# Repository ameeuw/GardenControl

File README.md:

# GardenControl

This project combines three mechanical relay switches with modular sensor ports in a case to allow for automated watering, lighting and nutritioning of plants.

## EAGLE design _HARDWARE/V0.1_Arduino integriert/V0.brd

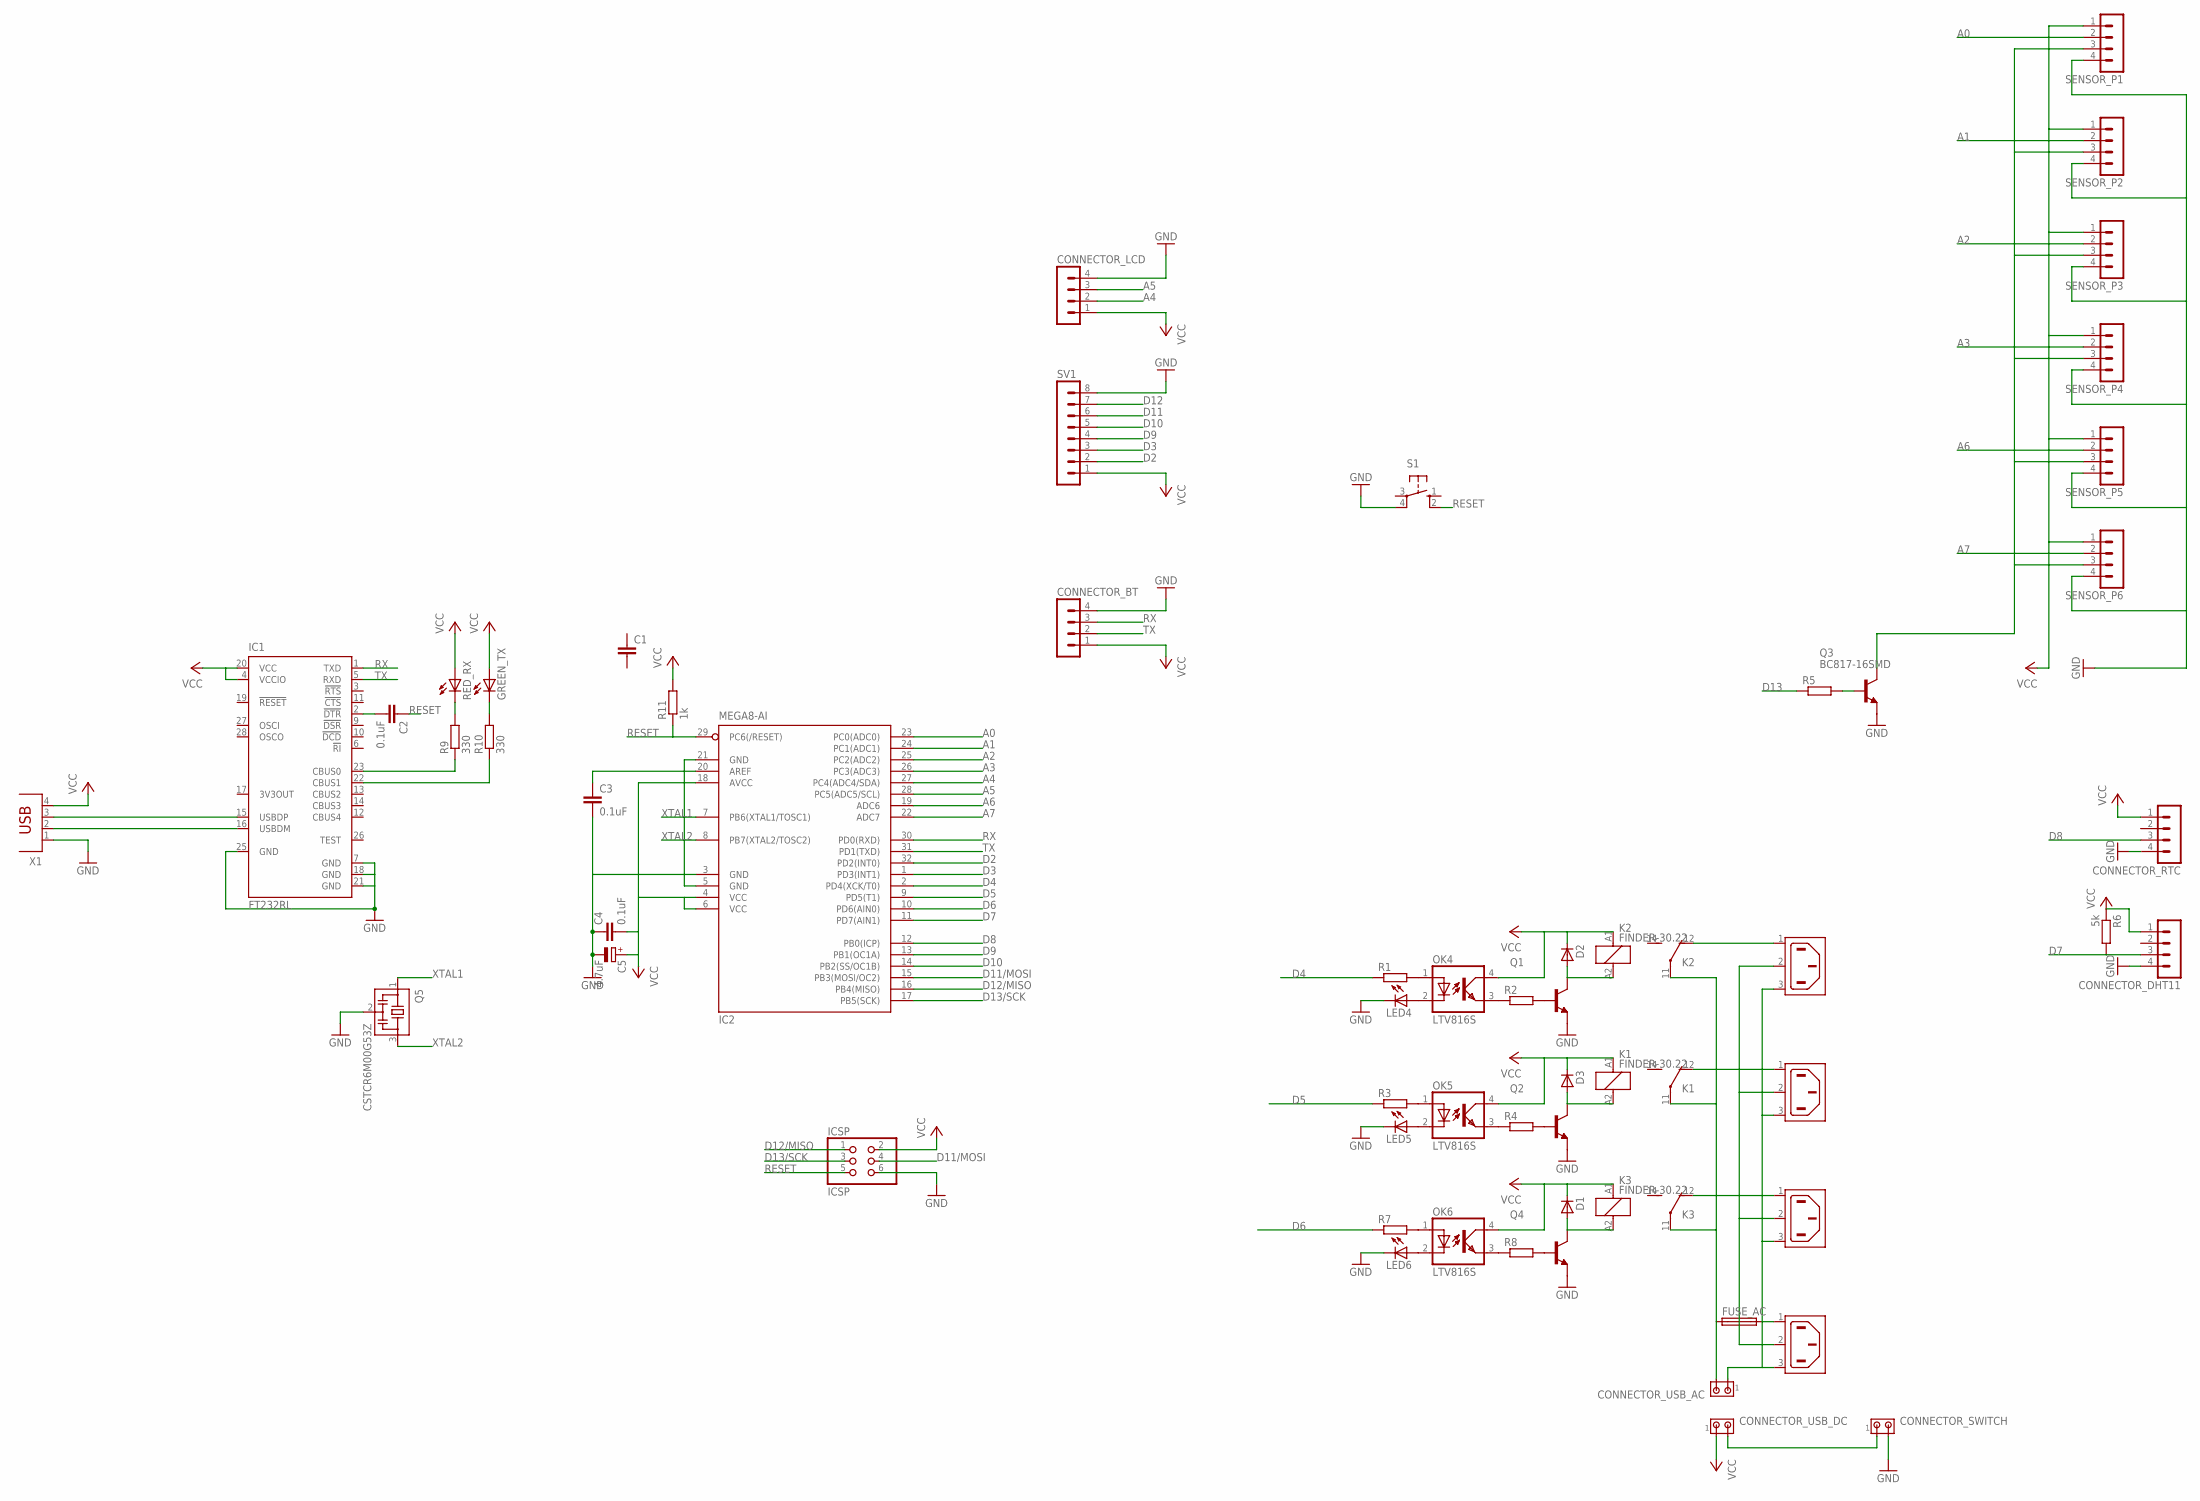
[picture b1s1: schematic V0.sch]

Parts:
C1: C; C0805
C2, C3, C4: 0.1uF; C0805
C5: 4.7uF; 085CS_1AW
CONNECTOR_BT: MA04-1
CONNECTOR_DHT11: MA04-1
CONNECTOR_LCD: MA04-1
CONNECTOR_RTC: MA04-1
CONNECTOR_SWITCH: MTA02-100; 10X02MTA
CONNECTOR_USB_AC: MTA02-100; 10X02MTA
CONNECTOR_USB_DC: MTA02-100; 10X02MTA
D1, D2, D3: DIODE_E-; DIODE_SMB
FUSE_AC: SH22,5
GREEN_TX: LEDCHIPLED_0805; CHIPLED_0805
IC1: FT232RL; SSOP28
IC2: MEGA8-AI; TQFP32-08
ICSP: ICSP; 2X03SMD
IN_AC: 6ESRM-P
K1, K2, K3: FINDER-30.22
LED4, LED5, LED6: LEDCHIPLED_0805; CHIPLED_0805
OK4, OK5, OK6: LTV816S; SMD4
OUT_LIGHT: 6ESRM-P
OUT_PUMP, OUT_PUMP1: 6ESRM-P
Q1, Q2, Q4: BC847ASMD; SOT23
Q3: BC817-16SMD; SOT23-BEC
Q5: CSTCR6M00G53Z; CSTCR6M
R1, R2, R3, R4, R5, R7, R8: R; R0805
R6: 5k; R0805
R9, R10: 330; R0805
R11: 1k; R0805
RED_RX: LEDCHIPLED_0805; CHIPLED_0805
S1: 10-XX; B3F-10XX
SENSOR_P1, SENSOR_P2, SENSOR_P3, SENSOR_P4, SENSOR_P5, SENSOR_P6: MA04-1
SV1: MA08-1
X1: PN61729

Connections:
A0: IC2.23 (PC0(ADC0)), SENSOR_P1.2
A1: IC2.24 (PC1(ADC1)), SENSOR_P2.2
A2: IC2.25 (PC2(ADC2)), SENSOR_P3.2
A3: IC2.26 (PC3(ADC3)), SENSOR_P4.2
A4: CONNECTOR_LCD.2, IC2.27 (PC4(ADC4/SDA))
A5: CONNECTOR_LCD.3, IC2.28 (PC5(ADC5/SCL))
A6: IC2.19 (ADC6), SENSOR_P5.2
A7: IC2.22 (ADC7), SENSOR_P6.2
AVCC: IC2.18 (AVCC)
D2: IC2.32 (PD2(INT0)), SV1.2
D3: IC2.1 (PD3(INT1)), SV1.3
D4: IC2.2 (PD4(XCK/T0)), R1.1
D5: IC2.9 (PD5(T1)), R3.1
D6: IC2.10 (PD6(AIN0)), R7.1
D7: CONNECTOR_DHT11.3, IC2.11 (PD7(AIN1)), R6.2
D8: CONNECTOR_RTC.3, IC2.12 (PB0(ICP))
D9: IC2.13 (PB1(OC1A)), SV1.4
D10: IC2.14 (PB2(SS/OC1B)), SV1.5
D11: SV1.6
D11/MOSI: IC2.15 (PB3(MOSI/OC2)), ICSP.4
D12: SV1.7
D12/MISO: IC2.16 (PB4(MISO)), ICSP.1
D13: R5.1
D13/SCK: IC2.17 (PB5(SCK)), ICSP.3
GND: C3.2, C4.1, C5.-, CONNECTOR_BT.4, CONNECTOR_DHT11.4, CONNECTOR_LCD.4, CONNECTOR_RTC.4, CONNECTOR_SWITCH.2, IC1.7 (GND), IC1.18 (GND), IC1.21 (GND), IC1.25 (GND), IC2.3 (GND), IC2.5 (GND), IC2.21 (GND), ICSP.6, LED4.C, LED5.C, LED6.C, Q1.2 (E), Q2.2 (E), Q3.E, Q4.2 (E), Q5.2, S1.4 (P1), SENSOR_P1.4, SENSOR_P2.4, SENSOR_P3.4, SENSOR_P4.4, SENSOR_P5.4, SENSOR_P6.4, SV1.8, X1.1
unnamed: OK4.1 (A), R1.2
unnamed: OK5.1 (A), R3.2
unnamed: OK6.1 (A), R7.2
unnamed: D2.A (C), K2.A2 (2), Q1.3 (C)
unnamed: R9.2, RED_RX.C
unnamed: Q1.1 (B), R2.2
unnamed: CONNECTOR_USB_AC.2, FUSE_AC.1, K1.11, K2.11, K3.11
unnamed: IN_AC.2 (SH), OUT_LIGHT.2 (SH), OUT_PUMP.2 (SH), OUT_PUMP1.2 (SH)
unnamed: LED4.A, OK4.2 (C)
unnamed: FUSE_AC.2, IN_AC.1 (AC1)
unnamed: LED5.A, OK5.2 (C)
unnamed: LED6.A, OK6.2 (C)
unnamed: D3.A (C), K1.A2 (2), Q2.3 (C)
unnamed: GREEN_TX.C, R10.2
unnamed: Q2.1 (B), R4.2
unnamed: K1.12 (O), OUT_PUMP.1 (AC1)
unnamed: K2.12 (O), OUT_LIGHT.1 (AC1)
unnamed: CONNECTOR_USB_AC.1, IN_AC.3 (AC2), OUT_LIGHT.3 (AC2), OUT_PUMP.3 (AC2), OUT_PUMP1.3 (AC2)
unnamed: Q3.C, SENSOR_P1.3, SENSOR_P2.3, SENSOR_P3.3, SENSOR_P4.3, SENSOR_P5.3, SENSOR_P6.3
unnamed: Q3.B, R5.2
unnamed: OK4.3 (EMIT), R2.1
unnamed: OK5.3 (EMIT), R4.1
unnamed: C2.2, IC1.2 (!DTR)
unnamed: IC1.23 (CBUS0), R9.1
unnamed: OK6.3 (EMIT), R8.1
unnamed: D1.A (C), K3.A2 (2), Q4.3 (C)
unnamed: IC1.22 (CBUS1), R10.1
unnamed: Q4.1 (B), R8.2
unnamed: K3.12 (O), OUT_PUMP1.1 (AC1)
unnamed: CONNECTOR_SWITCH.1, CONNECTOR_USB_DC.2
unnamed: IC1.15 (USBDP), X1.3
unnamed: IC1.16 (USBDM), X1.2
RESET: C2.1, IC2.29 (PC6(/RESET)), ICSP.5, R11.1, S1.2 (S1)
RX: CONNECTOR_BT.3, IC1.1 (TXD), IC2.30 (PD0(RXD))
TX: CONNECTOR_BT.2, IC1.5 (RXD), IC2.31 (PD1(TXD))
VCC: C4.2, C5.+, CONNECTOR_BT.1, CONNECTOR_DHT11.1, CONNECTOR_LCD.1, CONNECTOR_RTC.1, CONNECTOR_USB_DC.1, D1.C (A), D2.C (A), D3.C (A), GREEN_TX.A, IC1.4 (VCCIO), IC1.20 (VCC), IC2.4 (VCC), IC2.6 (VCC), ICSP.2, K1.A1 (1), K2.A1 (1), K3.A1 (1), OK4.4 (COL), OK5.4 (COL), OK6.4 (COL), R6.1, R11.2, RED_RX.A, SENSOR_P1.1, SENSOR_P2.1, SENSOR_P3.1, SENSOR_P4.1, SENSOR_P5.1, SENSOR_P6.1, SV1.1, X1.4
XTAL1: IC2.7 (PB6(XTAL1/TOSC1)), Q5.1
XTAL2: IC2.8 (PB7(XTAL2/TOSC2)), Q5.3

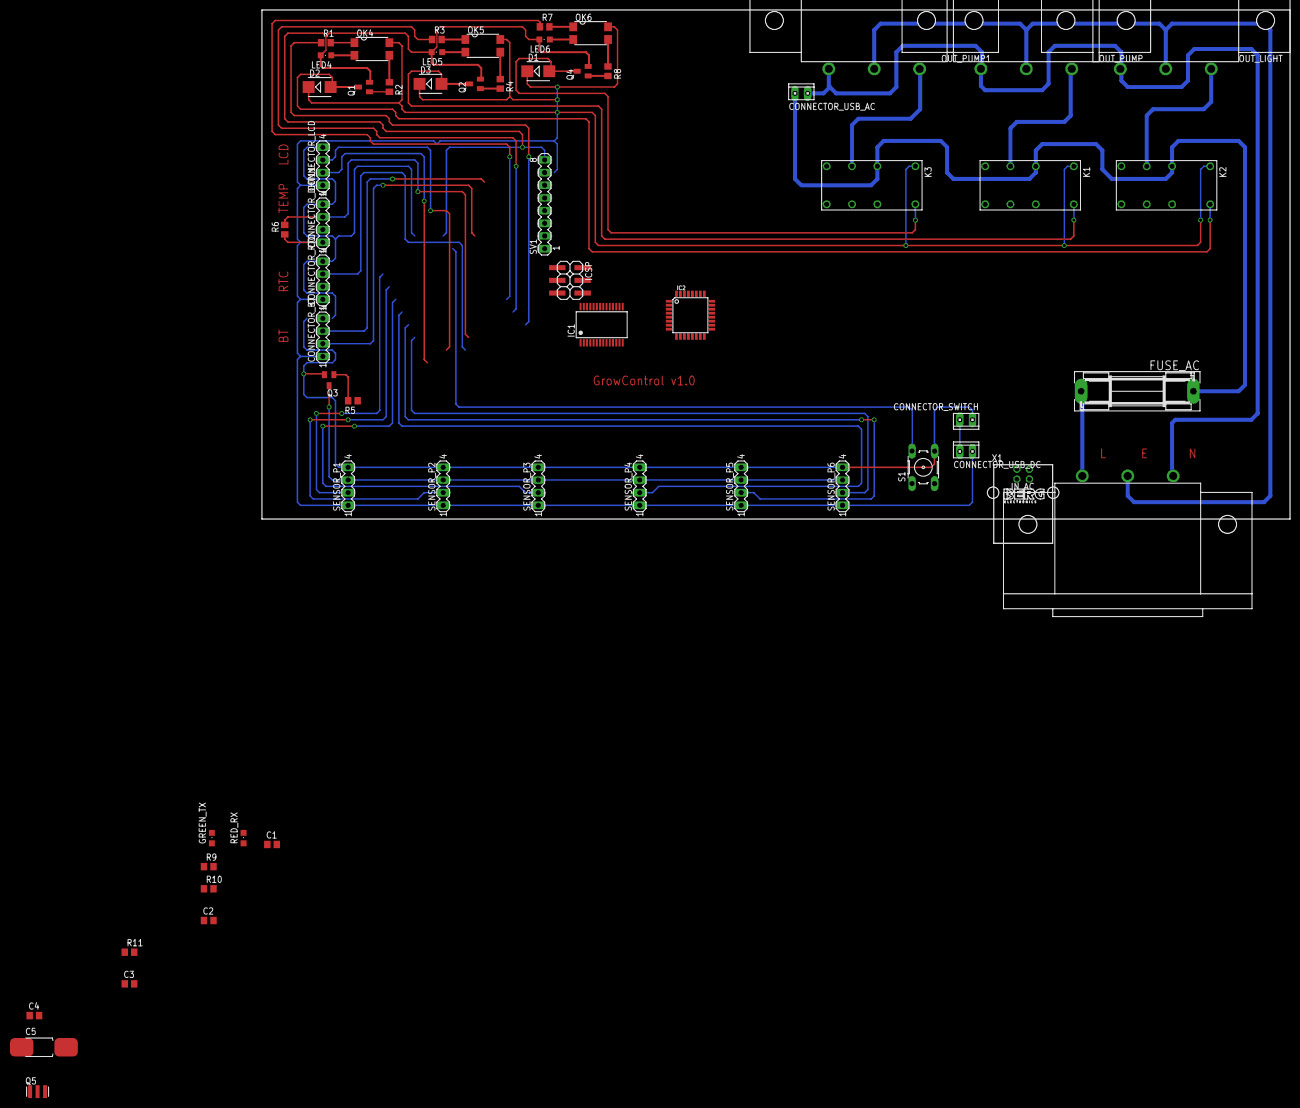
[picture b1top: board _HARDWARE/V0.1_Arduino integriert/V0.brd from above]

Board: 2 copper layers, 206.0 x 102.0 mm, 59 parts (0 on the bottom side), 59 nets.

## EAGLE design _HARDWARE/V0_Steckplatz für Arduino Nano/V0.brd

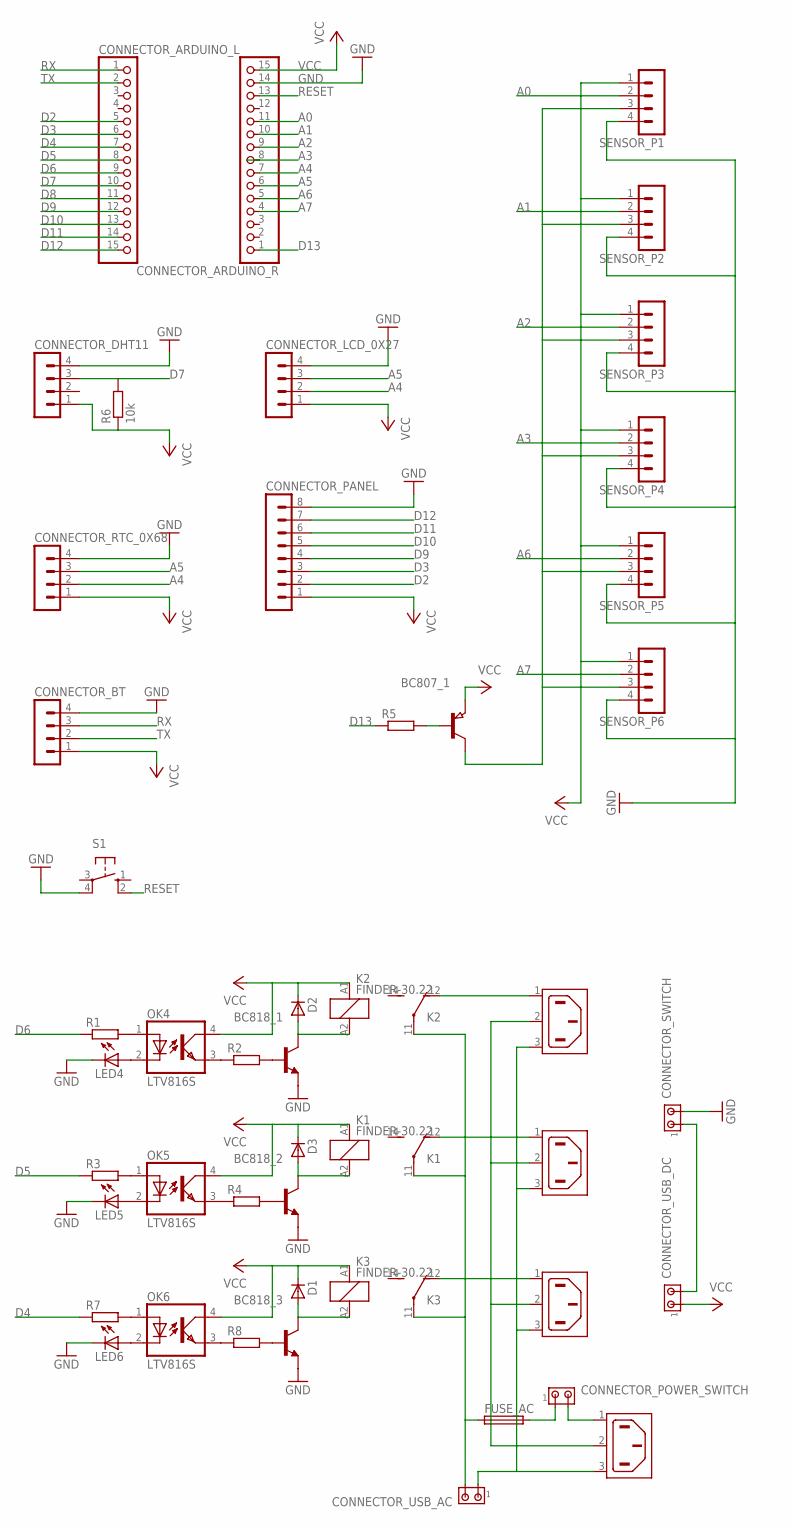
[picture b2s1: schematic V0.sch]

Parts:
BC807_1: PNP-TRANSISTOR_SOT23; SOT23
BC818_1, BC818_2, BC818_3: BC847ASMD; SOT23
CONNECTOR_ARDUINO_L: PINHD-1X15; 1X15
CONNECTOR_ARDUINO_R: PINHD-1X15; 1X15
CONNECTOR_BT: MA04-1
CONNECTOR_DHT11: MA04-1
CONNECTOR_LCD_0X27: MA04-1
CONNECTOR_PANEL: MA08-1
CONNECTOR_POWER_SWITCH: MTA02-100; 10X02MTA
CONNECTOR_RTC_0X68: MA04-1
CONNECTOR_SWITCH: MTA02-100; 10X02MTA
CONNECTOR_USB_AC: MTA02-100; 10X02MTA
CONNECTOR_USB_DC: MTA02-100; 10X02MTA
D1, D2, D3: DIODE_E-; DIODE_SMB
FUSE_AC: SH22,5
IN_AC: 6ESRM-P
K1, K2, K3: FINDER-30.22
LED4, LED5, LED6: LEDCHIPLED_0805; CHIPLED_0805
OK4, OK5, OK6: LTV816S; SMD4
OUT_LIGHT: 6ESRM-P
OUT_PUMP, OUT_PUMP1: 6ESRM-P
R1, R2, R3, R4, R5, R7, R8: R; R0805
R6: 10k; R0805
S1: 10-XX; B3F-10XX
SENSOR_P1, SENSOR_P2, SENSOR_P3, SENSOR_P4, SENSOR_P5, SENSOR_P6: MA04-1

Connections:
A0: CONNECTOR_ARDUINO_R.11, SENSOR_P1.2
A1: CONNECTOR_ARDUINO_R.10, SENSOR_P2.2
A2: CONNECTOR_ARDUINO_R.9, SENSOR_P3.2
A3: CONNECTOR_ARDUINO_R.8, SENSOR_P4.2
A4: CONNECTOR_ARDUINO_R.7, CONNECTOR_LCD_0X27.2, CONNECTOR_RTC_0X68.2
A5: CONNECTOR_ARDUINO_R.6, CONNECTOR_LCD_0X27.3, CONNECTOR_RTC_0X68.3
A6: CONNECTOR_ARDUINO_R.5, SENSOR_P5.2
A7: CONNECTOR_ARDUINO_R.4, SENSOR_P6.2
D2: CONNECTOR_ARDUINO_L.5, CONNECTOR_PANEL.2
D3: CONNECTOR_ARDUINO_L.6, CONNECTOR_PANEL.3
D4: CONNECTOR_ARDUINO_L.7, R7.1
D5: CONNECTOR_ARDUINO_L.8, R3.1
D6: CONNECTOR_ARDUINO_L.9, R1.1
D7: CONNECTOR_ARDUINO_L.10, CONNECTOR_DHT11.3, R6.2
D8: CONNECTOR_ARDUINO_L.11
D9: CONNECTOR_ARDUINO_L.12, CONNECTOR_PANEL.4
D10: CONNECTOR_ARDUINO_L.13, CONNECTOR_PANEL.5
D11: CONNECTOR_ARDUINO_L.14, CONNECTOR_PANEL.6
D12: CONNECTOR_ARDUINO_L.15, CONNECTOR_PANEL.7
D13: CONNECTOR_ARDUINO_R.1, R5.1
GND: BC818_1.2 (E), BC818_2.2 (E), BC818_3.2 (E), CONNECTOR_ARDUINO_R.14, CONNECTOR_BT.4, CONNECTOR_DHT11.4, CONNECTOR_LCD_0X27.4, CONNECTOR_PANEL.8, CONNECTOR_RTC_0X68.4, CONNECTOR_SWITCH.2, LED4.C, LED5.C, LED6.C, S1.4 (P1), SENSOR_P1.4, SENSOR_P2.4, SENSOR_P3.4, SENSOR_P4.4, SENSOR_P5.4, SENSOR_P6.4
unnamed: OK4.1 (A), R1.2
unnamed: OK5.1 (A), R3.2
unnamed: OK6.1 (A), R7.2
unnamed: BC818_1.3 (C), D2.A (C), K2.A2 (2)
unnamed: BC818_1.1 (B), R2.2
unnamed: CONNECTOR_USB_AC.2, FUSE_AC.1, K1.11, K2.11, K3.11
unnamed: IN_AC.2 (SH), OUT_LIGHT.2 (SH), OUT_PUMP.2 (SH), OUT_PUMP1.2 (SH)
unnamed: LED4.A, OK4.2 (C)
unnamed: CONNECTOR_POWER_SWITCH.2, IN_AC.1 (AC1)
unnamed: LED5.A, OK5.2 (C)
unnamed: LED6.A, OK6.2 (C)
unnamed: BC818_2.3 (C), D3.A (C), K1.A2 (2)
unnamed: CONNECTOR_POWER_SWITCH.1, FUSE_AC.2
unnamed: BC818_2.1 (B), R4.2
unnamed: K1.12 (O), OUT_PUMP.1 (AC1)
unnamed: K2.12 (O), OUT_LIGHT.1 (AC1)
unnamed: CONNECTOR_USB_AC.1, IN_AC.3 (AC2), OUT_LIGHT.3 (AC2), OUT_PUMP.3 (AC2), OUT_PUMP1.3 (AC2)
unnamed: BC807_1.3 (C), SENSOR_P1.3, SENSOR_P2.3, SENSOR_P3.3, SENSOR_P4.3, SENSOR_P5.3, SENSOR_P6.3
unnamed: BC807_1.1 (B), R5.2
unnamed: OK4.3 (EMIT), R2.1
unnamed: OK5.3 (EMIT), R4.1
unnamed: OK6.3 (EMIT), R8.1
unnamed: BC818_3.3 (C), D1.A (C), K3.A2 (2)
unnamed: BC818_3.1 (B), R8.2
unnamed: K3.12 (O), OUT_PUMP1.1 (AC1)
unnamed: CONNECTOR_SWITCH.1, CONNECTOR_USB_DC.2
RESET: CONNECTOR_ARDUINO_R.13, S1.2 (S1)
RX: CONNECTOR_ARDUINO_L.1, CONNECTOR_BT.3
TX: CONNECTOR_ARDUINO_L.2, CONNECTOR_BT.2
VCC: BC807_1.2 (E), CONNECTOR_ARDUINO_R.15, CONNECTOR_BT.1, CONNECTOR_DHT11.1, CONNECTOR_LCD_0X27.1, CONNECTOR_PANEL.1, CONNECTOR_RTC_0X68.1, CONNECTOR_USB_DC.1, D1.C (A), D2.C (A), D3.C (A), K1.A1 (1), K2.A1 (1), K3.A1 (1), OK4.4 (COL), OK5.4 (COL), OK6.4 (COL), R6.1, SENSOR_P1.1, SENSOR_P2.1, SENSOR_P3.1, SENSOR_P4.1, SENSOR_P5.1, SENSOR_P6.1

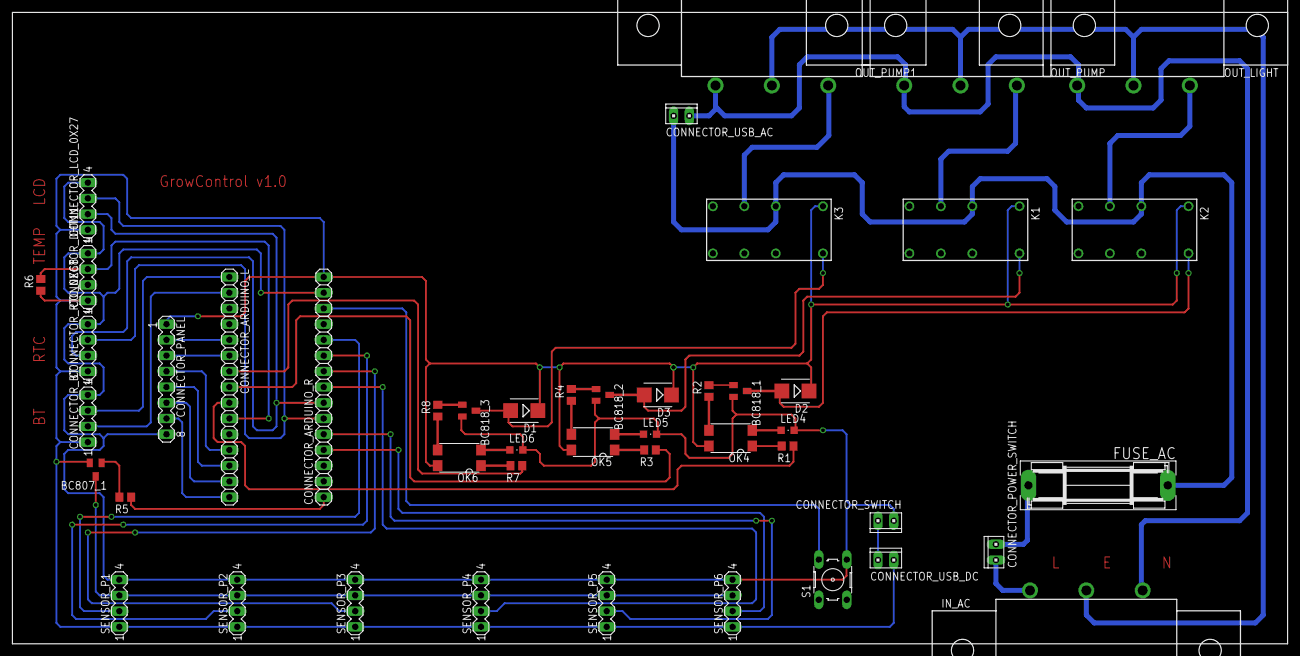
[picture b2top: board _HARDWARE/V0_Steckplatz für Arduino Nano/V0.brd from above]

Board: 2 copper layers, 206.0 x 102.0 mm, 47 parts (0 on the bottom side), 50 nets.

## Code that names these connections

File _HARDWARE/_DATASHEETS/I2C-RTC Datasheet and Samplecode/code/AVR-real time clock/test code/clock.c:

//Function: Display: seconds, minutes, weeks, days, date, month, year. Can show :2000-2099.
//Note: DS1307 to read and write are the BCD code, the use of a swap between the decimal and BCD code.
//Platform£ºatmega64
//fuse bytes£º
//		  low byte£º0xc1
//		  high byte£º0xd9
//		  extend£º0xFF
//		  Lock byte£º0xff
//Crystal Oscillator: Internal RC oscillator 1MHz
//Time: July 27, 2012
#include<avr/io.h>
#include <macros.h>
#include <avr/wdt.h>
#define uint unsigned int 
#define uchar unsigned char
//sda=PD1;//;TWI Data transmission bit
//scl=PD0;//;TWI Clock control state flag
//RS=PC0;//define the I / O hardware interface of LCD1602
//RW=PC1;//define the I / O hardware interface 0f LCD1602 
//E=PC2; //define the I / O hardware interface 0f LCD1602 
uchar count;
uchar string3[]="Time:  :  :     ";
uchar string4[]="20  .  .  week: ";
uchar Hours=16;//Definition of hours
uchar Minutes=21;//Definition of minutes
uchar Seconds=0;//Definition of seconds

uint  Year=12;//Definition of year
uchar Month=7;//Definition of month
uchar Date=27;//Definition of date
uchar Weeks=5;//Definition of weeks 

uchar DispBuf[16]; //16 bytes of display buffer
uchar disp_tab[]={'0','1','2','3','4','5','6','7','8','9'};

#define START 		0X08   //start() has been successfully sent
#define RESTART 	0X10 //The restart() has been successfully sent
#define MT_SLA_ACK 	0X18 //Load data has been sent ack()
#define MT_SLA_NACK 0X20 //Load data has been sent nack()
#define MT_DAT_ACK 	0X28  //Data has been sent ack()
#define MT_DAT_NACK 0X30 //Data has been sent nack()
#define SL_SLA_ACK 	0X40 //Data has been loaded from the machine to send ack()
#define SL_SLA_NACK 0X48 //Data has been loaded from the machine to send nack()
#define SL_DAT_ACK 	0X50  //Slave data has been sent ack()
#define SL_DAT_NACK 0X58  //Slave data has been sent nack()

#define start() 	TWCR=((1<<TWINT)|(1<<TWSTA)|(1<<TWEN)) //Send start signal
#define restart() 	TWCR=((1<<TWINT)|(1<<TWEN)|(1<<TWSTA)) //Sent to re-start signal
#define wait()  	while(!(TWCR & (1<<TWINT))) //Waiting for the signal
#define state() 	(TWSR&0XF8) //The register TWSR state extraction
#define stop() 		TWCR=((1<<TWEN)|(1<<TWINT)|(1<<TWSTO)) //Stop signal
#define twi()		(TWCR=(1<<TWINT)|(1<<TWEN))	//Open the TWI function
#define setnoAck()	(TWCR&=~(1<<TWEA))				//Make Not Ack response

#define r_direction 0xD1 //Read the device address
#define w_direction 0xD0 //Write device address

void twi_init()  //TWI initialization
{
   TWCR |=(1<<TWEN); //Start twi function
   TWBR=0X20;  //Set the baud rate for the host mode
   TWSR=0;    //Clear Status Register
}

void writebyte(uchar temp)//A byte data write to the TWI
{
	TWDR=temp;
	TWCR=((1<<TWINT)|(1<<TWEN));
}
uchar TWI_Write(uchar addr,uchar dat) //Write data to TWI
{
   start();//start signal
   wait();//Start TWI function
   if(state()!=START)//Wait for the nack/ack() signal
   return 1;

   writebyte(w_direction);//write    Device address
   wait();
   if(state()!=MT_SLA_ACK)
   return 1;

   writebyte(addr);//write      Byte address
   wait();
   if(state()!=MT_DAT_ACK)
   return 1;

   writebyte(dat);//write     data
   wait();
   if(state()!=MT_DAT_ACK)
   return 1;

   stop();//stop signal
   return 0;
}

uchar TWI_Read(uchar addr) //Read data from TWI
{
   	uchar temp=0;
   	start();//
	wait();
	if(state()!=START) 
	return 1;			 		//ACK*/	   

	writebyte(w_direction);	//Write TWI slave address and write
	wait(); 
	if(state()!=MT_SLA_ACK) 
	return 1;				    //ACK*/

	writebyte(addr);		//Write the corresponding device register address
	wait();
	if(state()!=MT_DAT_ACK) 
	return 1;//*/

	start();	   				   	//TWI re-start
	wait();
	if (state()!=RESTART)  
	return 1;//*/

	writebyte(r_direction);	//Write TWI slave device address and read
	wait();
	if(state()!=SL_SLA_ACK)  
	return 1;				   //ACK*/

	twi();	 				   //Start the TWI read
	wait();
	if(state()!=SL_DAT_NACK) 
	return 1;					//ACK*/	

	temp=TWDR;//Read the TWI of the receive data
	stop();//
	return temp;


}
/////////////////////////////////////////
//////////////////////////////////////////
uchar Decimal_to_BCD(uchar temp)//Decimal converted to BCD code
{
	uchar a,b,c;
	a=temp;
	b=0x00;
	if(a>=10)
	{
		while(a>=10)
		{
			a=a-10;
			b=b+16;
			c=a+b;
			temp=c;
		}
	}
	return temp;
}

uchar BCD_to_Decimal(uchar temp)//BCD to decimal
{
	uchar a,b,c;
	a=temp;
	b=0x00;
	if(a>=16)
	{
		while(a>=16)
		{
			a=a-16;
			b=b+10;
			c=a+b;
			temp=c;
		}
	}
	return temp;
}
////////////////////////////////////////	
void delay_2(uint z)//0.1msDelay
{ 
	uchar x,x1;
	for(x1=0;x1<z;x1++)
	{
		for(x=0;x<114;x++);
	}
}

void delay_1()//0.1msDelay
{ 
	uchar x,x1;
	for(x1=0;x1<2;x1++)
	{
		for(x=0;x<100;x++);
	}
}
///////////LCD1602///////////////////
/////////////////////////////////////
void write_Directive(uchar command)//Write command
{
	PORTC &=~(1<<PC2);//E=0;
	PORTC &=~(1<<PC0);//RS=0;
	PORTC &=~(1<<PC1);//RW=0;	
	PORTA = command;
	PORTC |=(1<<PC2);//E=1;	
	delay_1();
	PORTC &=~(1<<PC2);//E=0;
}
void write_Data(uchar dat)//write data
{
	PORTC &=~(1<<PC2);//E=0;
	PORTC |=(1<<PC0);//RS=1;
	PORTC &=~(1<<PC1);//RW=0;
	PORTA = dat;
	PORTC |=(1<<PC2);//E=1;
	delay_1();
	PORTC &= ~(1<<PC2);//E=0;
}
void lcdinit(void)//Initialization
{
	delay_2(90);
	write_Directive(0x38);
	delay_2(30);
	write_Directive(0x38);
	delay_2(30);
	write_Directive(0x38);
	write_Directive(0x38);
	write_Directive(0x08);
	write_Directive(0x01);
	write_Directive(0x06);
	write_Directive(0x0c);		
}
void Show()//show
{ 
	write_Directive(0x80+5);//the first row of LCD1602 , The fifth address
	DispBuf[0]=disp_tab[(Hours/10)];//
	DispBuf[1]=disp_tab[(Hours%10)];//	
	write_Data(DispBuf[0]);//Ten of the Hours
	write_Data(DispBuf[1]);// Bits of the Hours

	write_Directive(0x80+8);
	DispBuf[2]=disp_tab[(Minutes/10)];//
	DispBuf[3]=disp_tab[(Minutes%10)];//	
	write_Data(DispBuf[2]);//Ten of the Minutes
	write_Data(DispBuf[3]);//Bits of the Minutes

	write_Directive(0x80+11);
	DispBuf[4]=disp_tab[(Seconds/10)];//
	DispBuf[5]=disp_tab[(Seconds%10)];//	
	write_Data(DispBuf[4]);//Ten of the Seconds
	write_Data(DispBuf[5]);//Bits of the Seconds
	
	write_Directive(0x80+0x40+2);//the second line of LCD1602, The second addresses
	DispBuf[7]=disp_tab[(Year/10)];//
	DispBuf[8]=disp_tab[(Year%10)];//
	write_Data(DispBuf[7]);//Ten of the Year
	write_Data(DispBuf[8]);//Bits of the Year
	
	write_Directive(0x80+0x40+5);//
	DispBuf[9]=disp_tab[(Month/10)];//
	DispBuf[10]=disp_tab[(Month%10)];//
	write_Data(DispBuf[9]);//Ten of the clock
	write_Data(DispBuf[10]);//Bits of the clock

	write_Directive(0x80+0x40+8);//
	DispBuf[11]=disp_tab[(Date/10)];//
	DispBuf[12]=disp_tab[(Date%10)];//
	write_Data(DispBuf[11]);//Ten of the Date
	write_Data(DispBuf[12]);//Bits of the Date

	write_Directive(0x80+0x40+15);//
	DispBuf[14]=disp_tab[Weeks];//
	write_Data(DispBuf[14]);//week
}

void write_ds1307()//write ds1307
{
	//Write a data to the device: (0xd0 is device write address; 0x01 ~ 06 are seconds to years register; Seconds ~ Year, data to be written)//
	Seconds=Decimal_to_BCD(Seconds);//Decimal converted to BCD code
	Minutes=Decimal_to_BCD(Minutes);//
	Hours=Decimal_to_BCD(Hours);//
	
	Date=Decimal_to_BCD(Date);//
	Year=Decimal_to_BCD(Year);//
	Month=Decimal_to_BCD(Month);//
	
	TWI_Write(0x00,Seconds);//write Seconds
	TWI_Write(0x01,Minutes);//write Minutes
	TWI_Write(0x02,Hours);//write Hours
	
	TWI_Write(0x03,Weeks);//write Weeks

	TWI_Write(0x04,Date);//write Data
	TWI_Write(0x05,Month);//write Month
	TWI_Write(0x06,Year);//write Year
}

void read_ds1307()//read ds1307
{
	//Read a data to the device: (0xd0 is the DS1307 device write address; 0x01 ~ 06 are seconds to years register; 0xd1 is DS1307 device read address) 
	Seconds=TWI_Read(0x00);
	Seconds=BCD_to_Decimal(Seconds);//BCD code converted to decimal
	
	Minutes=TWI_Read(0x01);
	Minutes=BCD_to_Decimal(Minutes);//
	WDR();

	Hours=TWI_Read(0x02);
	Hours=BCD_to_Decimal(Hours);//
	
	Weeks=TWI_Read(0x03);//
	WDR();	

	Date=TWI_Read(0x04);
	Date=BCD_to_Decimal(Date);//
	
	Month=TWI_Read(0x05);
	Month=BCD_to_Decimal(Month);//
	WDR();

	Year=TWI_Read(0x06);
	Year=BCD_to_Decimal(Year);//
}	

void display(uchar command,uchar dat)//Display data in the specified location of the LCD1602
{
	write_Directive(command);
	write_Data(dat);
}
int main(void)
{
	DDRA = 0XFF;//LCD1602 Data port
	DDRC = 0XFF;//LCD1602 Control port£ºRE,RW,E
	twi_init();//TWI Initialization
	lcdinit();	//LCD1602 Initialization
	
	write_Directive(0x80);//Display static data
	for(count=0;count<16;count++) write_Data(string3[count]);
	write_Directive(0x80+0x40);
	for(count=0;count<16;count++) write_Data(string4[count]);

	//write_ds1307();//Write the initial value on ds1307//(Modification time initial value when used)
	while(1)
	{ 
		read_ds1307();
		Show();//Display dynamic data
	}
}
